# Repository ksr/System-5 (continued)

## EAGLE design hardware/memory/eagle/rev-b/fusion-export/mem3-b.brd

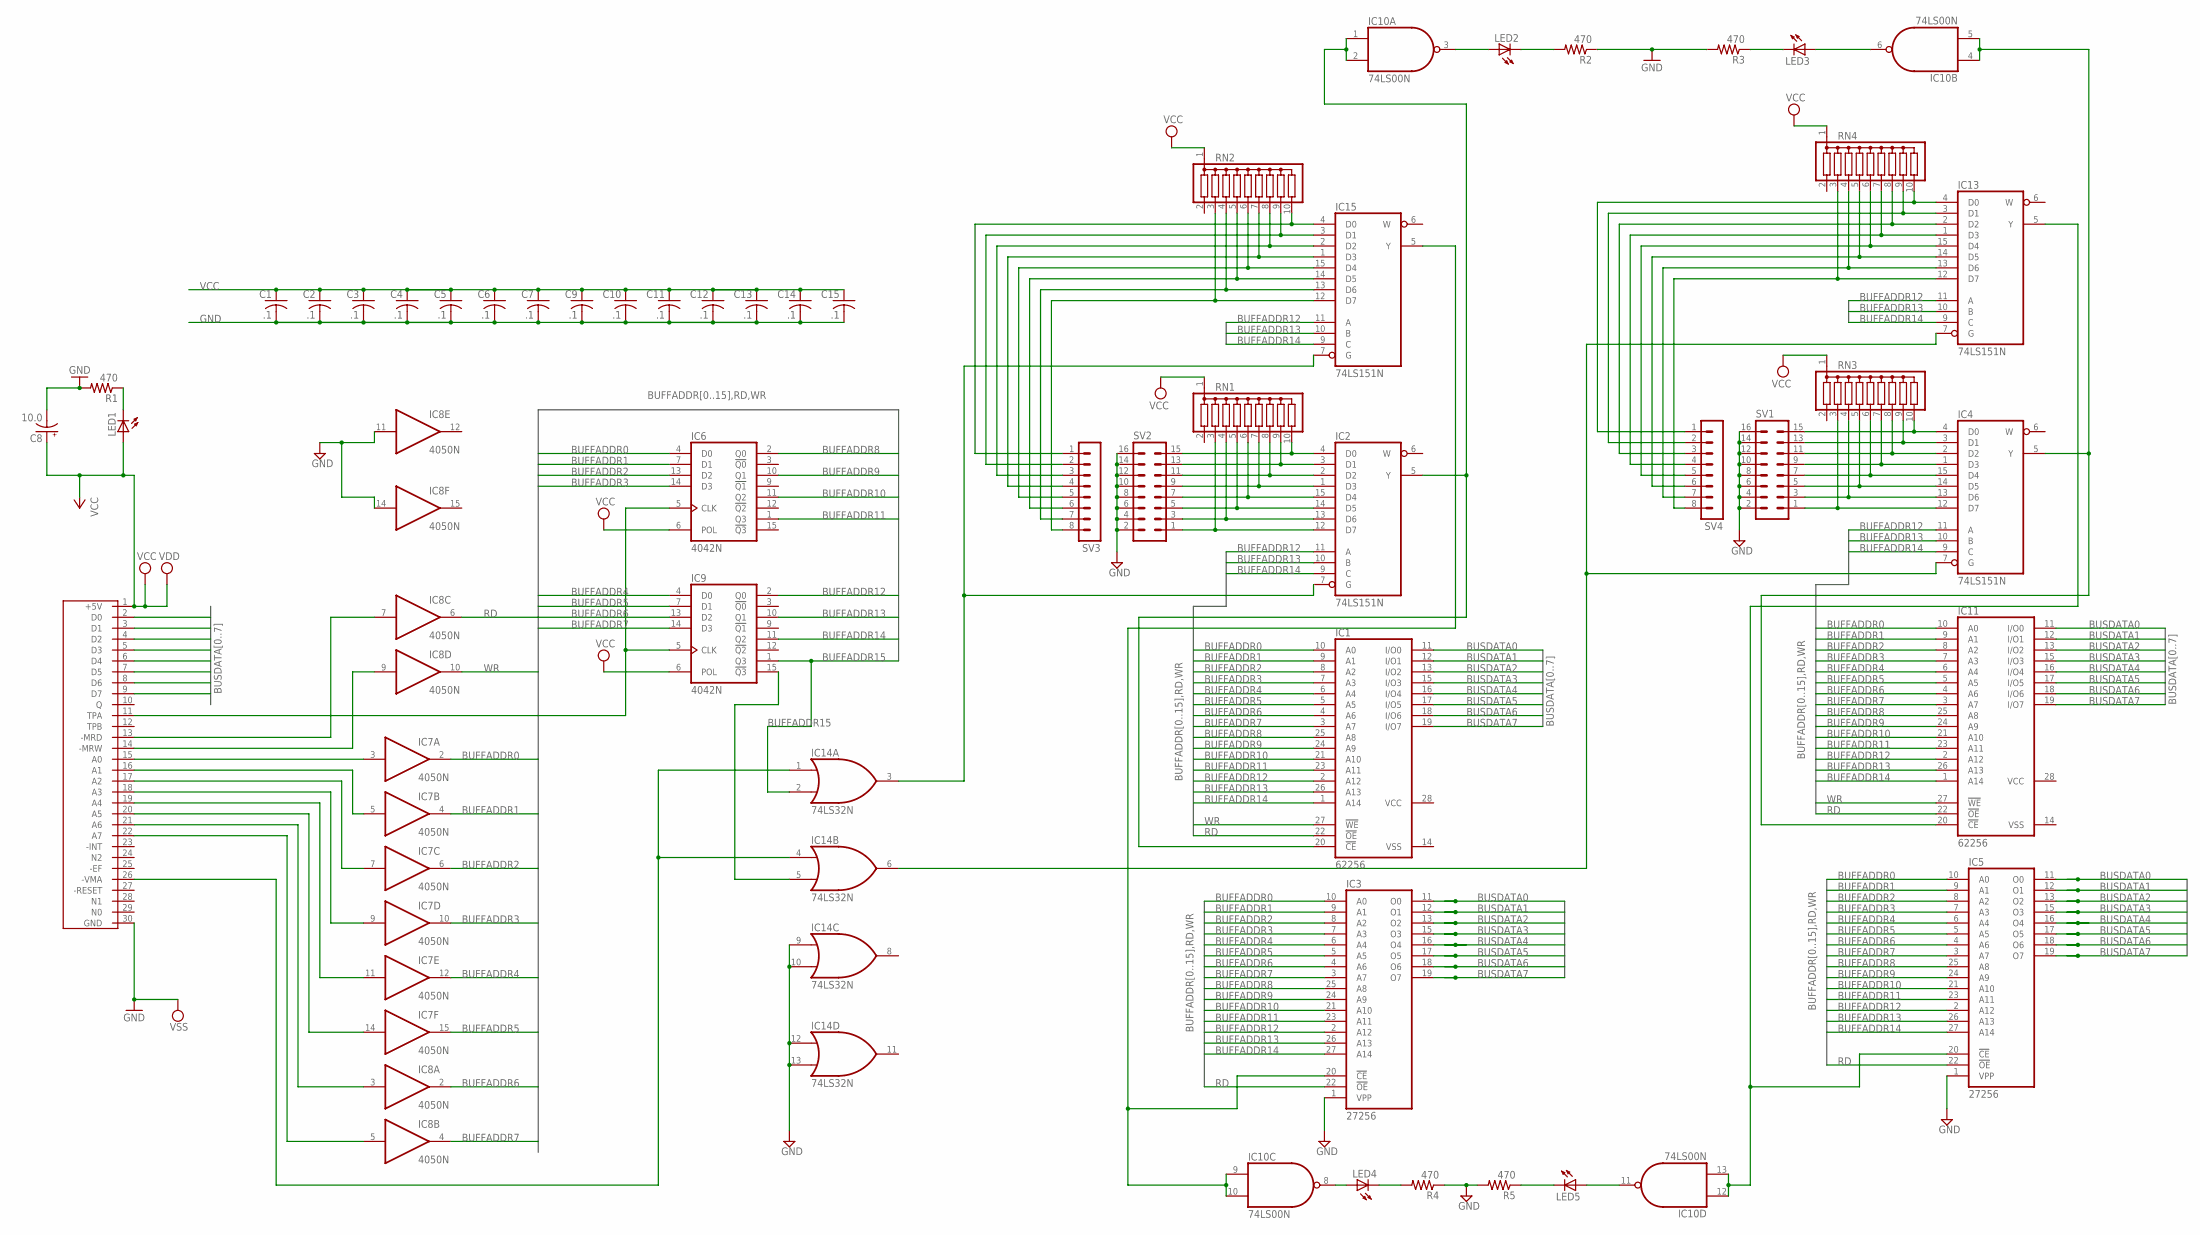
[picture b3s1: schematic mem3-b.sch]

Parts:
C1, C2, C3, C4, C5, C6, C7, C9, C10, C11, C12, C13, C14, C15: .1; C025-050X050
C8: 10.0; E2,5-7
IC1, IC11: 62256; DIL28-6
IC2, IC4, IC13, IC15: 74LS151N; DIL16
IC3, IC5: 27256; DIL28
IC6, IC9: 4042N; DIL16
IC7, IC8: 4050N; DIL16
IC10: 74LS00N; DIL14
IC14: 74LS32N; DIL14
LED1, LED2, LED3, LED4, LED5: LED5MM
R1, R2, R3, R4, R5: 470; 0207/7
RN1, RN2, RN3, RN4: G09R; SIL10
SV1, SV2: MA08-2
SV3, SV4: MA08-1
U$1: C30

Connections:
BUFFADDR0: IC1.10 (A0), IC3.10 (A0), IC5.10 (A0), IC6.4 (D0), IC7.2 (O), IC11.10 (A0)
BUFFADDR1: IC1.9 (A1), IC3.9 (A1), IC5.9 (A1), IC6.7 (D1), IC7.4 (O), IC11.9 (A1)
BUFFADDR2: IC1.8 (A2), IC3.8 (A2), IC5.8 (A2), IC6.13 (D2), IC7.6 (O), IC11.8 (A2)
BUFFADDR3: IC1.7 (A3), IC3.7 (A3), IC5.7 (A3), IC6.14 (D3), IC7.10 (O), IC11.7 (A3)
BUFFADDR4: IC1.6 (A4), IC3.6 (A4), IC5.6 (A4), IC7.12 (O), IC9.4 (D0), IC11.6 (A4)
BUFFADDR5: IC1.5 (A5), IC3.5 (A5), IC5.5 (A5), IC7.15 (O), IC9.7 (D1), IC11.5 (A5)
BUFFADDR6: IC1.4 (A6), IC3.4 (A6), IC5.4 (A6), IC8.2 (O), IC9.13 (D2), IC11.4 (A6)
BUFFADDR7: IC1.3 (A7), IC3.3 (A7), IC5.3 (A7), IC8.4 (O), IC9.14 (D3), IC11.3 (A7)
BUFFADDR8: IC1.25 (A8), IC3.25 (A8), IC5.25 (A8), IC6.2 (Q0), IC11.25 (A8)
BUFFADDR9: IC1.24 (A9), IC3.24 (A9), IC5.24 (A9), IC6.10 (Q1), IC11.24 (A9)
BUFFADDR10: IC1.21 (A10), IC3.21 (A10), IC5.21 (A10), IC6.11 (Q2), IC11.21 (A10)
BUFFADDR11: IC1.23 (A11), IC3.23 (A11), IC5.23 (A11), IC6.1 (Q3), IC11.23 (A11)
BUFFADDR12: IC1.2 (A12), IC2.11 (A), IC3.2 (A12), IC4.11 (A), IC5.2 (A12), IC9.2 (Q0), IC11.2 (A12), IC13.11 (A), IC15.11 (A)
BUFFADDR13: IC1.26 (A13), IC2.10 (B), IC3.26 (A13), IC4.10 (B), IC5.26 (A13), IC9.10 (Q1), IC11.26 (A13), IC13.10 (B), IC15.10 (B)
BUFFADDR14: IC1.1 (A14), IC2.9 (C), IC3.27 (A14), IC4.9 (C), IC5.27 (A14), IC9.11 (Q2), IC11.1 (A14), IC13.9 (C), IC15.9 (C)
BUFFADDR15: IC9.1 (Q3), IC14.2 (I1)
BUSDATA0: IC1.11 (I/O0), IC3.11 (O0), IC5.11 (O0), IC11.11 (I/O0), U$1.2 (D0)
BUSDATA1: IC1.12 (I/O1), IC3.12 (O1), IC5.12 (O1), IC11.12 (I/O1), U$1.3 (D1)
BUSDATA2: IC1.13 (I/O2), IC3.13 (O2), IC5.13 (O2), IC11.13 (I/O2), U$1.4 (D2)
BUSDATA3: IC1.15 (I/O3), IC3.15 (O3), IC5.15 (O3), IC11.15 (I/O3), U$1.5 (D3)
BUSDATA4: IC1.16 (I/O4), IC3.16 (O4), IC5.16 (O4), IC11.16 (I/O4), U$1.6 (D4)
BUSDATA5: IC1.17 (I/O5), IC3.17 (O5), IC5.17 (O5), IC11.17 (I/O5), U$1.7 (D5)
BUSDATA6: IC1.18 (I/O6), IC3.18 (O6), IC5.18 (O6), IC11.18 (I/O6), U$1.8 (D6)
BUSDATA7: IC1.19 (I/O7), IC3.19 (O7), IC5.19 (O7), IC11.19 (I/O7), U$1.9 (D7)
GND: C1.2, C2.2, C3.2, C4.2, C5.2, C6.2, C7.2, C8.-, C9.2, C10.2, C11.2, C12.2, C13.2, C14.2, C15.2, IC1.14 (VSS), IC2.8 (GND), IC3.1 (VPP), IC3.14 (GND), IC4.8 (GND), IC5.1 (VPP), IC5.14 (GND), IC6.8 (VSS), IC7.8 (VSS), IC8.8 (VSS), IC8.11 (I), IC8.14 (I), IC9.8 (VSS), IC10.7 (GND), IC11.14 (VSS), IC13.8 (GND), IC14.7 (GND), IC14.9 (I0), IC14.10 (I1), IC14.12 (I0), IC14.13 (I1), IC15.8 (GND), R1.2, R2.1, R3.2, R4.1, R5.2, SV1.2, SV1.4, SV1.6, SV1.8, SV1.10, SV1.12, SV1.14, SV1.16, SV2.2, SV2.4, SV2.6, SV2.8, SV2.10, SV2.12, SV2.14, SV2.16, U$1.30 (GND)
unnamed: LED1.K (C), R1.1
unnamed: IC2.12 (D7), RN1.3, SV2.1
unnamed: IC2.13 (D6), RN1.4, SV2.3
unnamed: IC2.14 (D5), RN1.5, SV2.5
unnamed: IC6.5 (CLK), IC9.5 (CLK), U$1.11 (TPA)
unnamed: IC2.15 (D4), RN1.6, SV2.7
unnamed: IC7.3 (I), U$1.15 (A0)
unnamed: IC7.5 (I), U$1.16 (A1)
unnamed: IC7.7 (I), U$1.17 (A2)
unnamed: IC7.9 (I), U$1.18 (A3)
unnamed: IC7.11 (I), U$1.19 (A4)
unnamed: IC7.14 (I), U$1.20 (A5)
unnamed: IC8.3 (I), U$1.21 (A6)
unnamed: IC8.5 (I), U$1.22 (A7)
unnamed: IC2.1 (D3), RN1.7, SV2.9
unnamed: IC2.2 (D2), RN1.8, SV2.11
unnamed: IC2.3 (D1), RN1.9, SV2.13
unnamed: IC2.4 (D0), RN1.10, SV2.15
unnamed: IC10.8 (O), LED4.A
unnamed: IC4.7 (G), IC13.7 (G), IC14.6 (O)
unnamed: IC4.12 (D7), RN3.3, SV1.1
unnamed: IC4.13 (D6), RN3.4, SV1.3
unnamed: IC4.14 (D5), RN3.5, SV1.5
unnamed: IC4.15 (D4), RN3.6, SV1.7
unnamed: IC8.9 (I), U$1.14 (-MRW)
unnamed: IC8.7 (I), U$1.13 (-MRD)
unnamed: IC14.1 (I0), IC14.4 (I0), U$1.26 (-VMA)
unnamed: IC4.1 (D3), RN3.7, SV1.9
unnamed: IC4.2 (D2), RN3.8, SV1.11
unnamed: IC4.3 (D1), RN3.9, SV1.13
unnamed: LED4.K (C), R4.2
unnamed: IC4.4 (D0), RN3.10, SV1.15
unnamed: IC1.20 (!CE), IC2.5 (Y), IC10.1 (I0), IC10.2 (I1)
unnamed: IC3.20 (!CE), IC10.9 (I0), IC10.10 (I1), IC15.5 (Y)
unnamed: IC13.13 (D6), RN4.4, SV4.7
unnamed: IC13.14 (D5), RN4.5, SV4.6
unnamed: IC13.15 (D4), RN4.6, SV4.5
unnamed: IC13.1 (D3), RN4.7, SV4.4
unnamed: IC13.2 (D2), RN4.8, SV4.3
unnamed: IC13.3 (D1), RN4.9, SV4.2
unnamed: IC13.12 (D7), RN4.3, SV4.8
unnamed: IC13.4 (D0), RN4.10, SV4.1
unnamed: IC5.20 (!CE), IC10.12 (I0), IC10.13 (I1), IC13.5 (Y)
unnamed: IC9.15 (!Q3), IC14.5 (I1)
unnamed: IC4.5 (Y), IC10.4 (I0), IC10.5 (I1), IC11.20 (!CE)
unnamed: IC2.7 (G), IC14.3 (O), IC15.7 (G)
unnamed: IC15.12 (D7), RN2.3, SV3.8
unnamed: LED5.K (C), R5.1
unnamed: IC10.11 (O), LED5.A
unnamed: IC10.3 (O), LED2.A
unnamed: LED2.K (C), R2.2
unnamed: IC15.13 (D6), RN2.4, SV3.7
unnamed: LED3.K (C), R3.1
unnamed: IC10.6 (O), LED3.A
unnamed: IC15.14 (D5), RN2.5, SV3.6
unnamed: IC15.15 (D4), RN2.6, SV3.5
unnamed: IC15.1 (D3), RN2.7, SV3.4
unnamed: IC15.2 (D2), RN2.8, SV3.3
unnamed: IC15.3 (D1), RN2.9, SV3.2
unnamed: IC15.4 (D0), RN2.10, SV3.1
RD: IC1.22 (!OE), IC3.22 (!OE), IC5.22 (!OE), IC8.6 (O), IC11.22 (!OE)
VCC: C1.1, C2.1, C3.1, C4.1, C5.1, C6.1, C7.1, C8.+, C9.1, C10.1, C11.1, C12.1, C13.1, C14.1, C15.1, IC1.28 (VCC), IC2.16 (VCC), IC3.28 (VCC), IC4.16 (VCC), IC5.28 (VCC), IC6.6 (POL), IC6.16 (VDD), IC7.1 (VDD), IC8.1 (VDD), IC9.6 (POL), IC9.16 (VDD), IC10.14 (VCC), IC11.28 (VCC), IC13.16 (VCC), IC14.14 (VCC), IC15.16 (VCC), LED1.A, RN1.1, RN2.1, RN3.1, RN4.1, U$1.1 (+5V)
WR: IC1.27 (!WE), IC8.10 (O), IC11.27 (!WE)

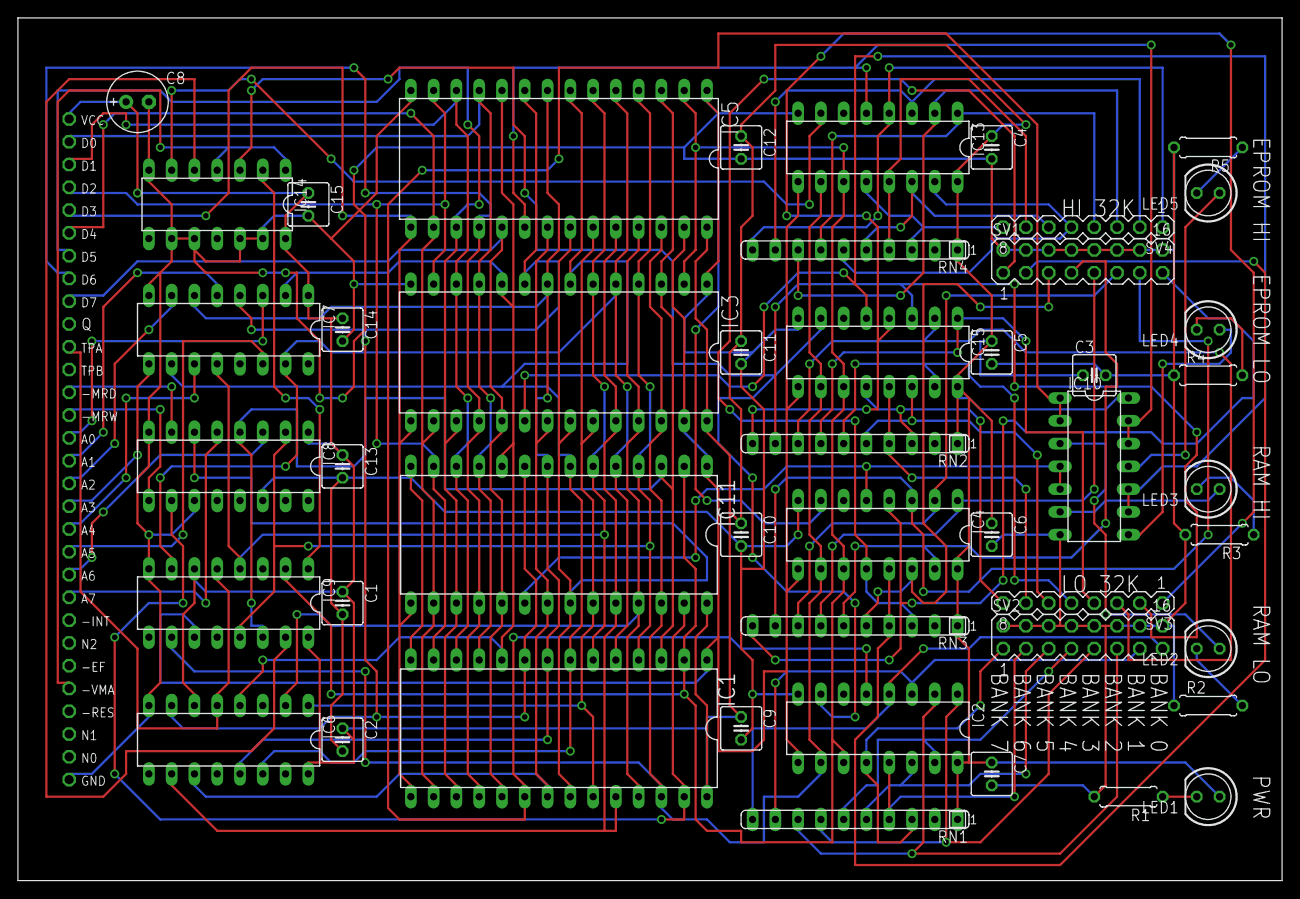
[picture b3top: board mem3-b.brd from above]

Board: 2 copper layers, 140.9 x 96.2 mm, 48 parts (0 on the bottom side), 88 nets.

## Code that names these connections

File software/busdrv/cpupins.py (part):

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Modes, from CLEAR and WAIT (the data sheet's table):
  RESET  CLEAR low, WAIT high   I, N, Q cleared, IE set; TPA and TPB held off; S1; the data bus driven to 00
  RUN    both high              after RESET one initialization cycle of 9 clock pulses (X, P and R(0) cleared), then S0
  PAUSE  CLEAR high, WAIT low   the timing generator stops: clock edges are ignored and every pin holds
  LOAD   both low               the idle S1 cycle over and over (M(R(0)) read, -MRD low); a DMA IN request is answered
                                by one S2 cycle (the bus byte written to M(R(0)), R(0) + 1), then idle again
Instructions are the emulator's (s5emu/cpu.py): each is worked out on a copy of the registers from the bytes the pins
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
    # ------------------------------------------------------------------ the pins
    def _reset_pins(self):
        self.A = 0; self.TPA = 0; self.TPB = 0; self.MRD = 1; self.MRW = 1; self.N = 0; self.Q = 0
        self.SC1, self.SC0 = 0, 1; self.D = 0x00            # RESET: S1, and 0's on the data bus
        self.e = 0; self.init = INIT_EDGES; self.cyc = None; self.dma_latch = False
        self._clear_instruction()
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
    # ------------------------------------------------------------------ CLEAR and WAIT (asynchronous)
    def set_mode(self, clear, wait):
        """the levels on the CLEAR and WAIT pins; -> True if any pin of the 1802 changed"""
        new = MODES[(1 if clear else 0, 1 if wait else 0)]
        if new == self.mode: return False
        old, self.mode = self.mode, new
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
    # ------------------------------------------------------------------ one transition of CLOCK
    def edge(self, dma_in=1, dbus=0xFF):
        """dma_in: the level on the DMA IN pin (0 = a request); dbus: what is on D0-D7 as this edge arrives"""
        if self.mode in ("reset", "pause"): return
        if self.init > CYCLE: self.init -= 1; return        # the initialization cycle's first two edges: nothing moves
        e = self.e
        if e == 0: self._start_cycle()
        c = self.cyc; kind = c["kind"]
        if e == 2: self.TPA = 1
        elif e == 3:
            if kind in READS: self.MRD = 0
        elif e == 4:
            self.TPA = 0
            if kind == "write": self.D = c["wd"]
        elif e == 5: self.A = c["addr"] & 0xFF
        elif e == 10:
            if kind in WRITES: self.MRW = 0
        elif e == 13:
            self.TPB = 1
            if self.dma_sample == 13 and not dma_in: self.dma_latch = True
        elif e == 14: self.MRW = 1
        elif e == 15:
            self.TPB = 0
            if self.dma_sample == 15 and not dma_in: self.dma_latch = True
            self._finish_cycle(dbus & 0xFF)
        self.e = (e + 1) % CYCLE
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            c = dict(kind="fetch", addr=core.R[core.P], n=0)
        self.cyc = c
        self.SC1, self.SC0 = SC[c["kind"]]
        self.A = c["addr"] >> 8; self.N = c["n"]; self.MRD = 1; self.MRW = 1; self.TPA = 0; self.TPB = 0
        self.D = 0x00 if c["kind"] == "init" else None      # (RESET's 00 stays on the data lines through that cycle)

    def _finish_cycle(self, data):
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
